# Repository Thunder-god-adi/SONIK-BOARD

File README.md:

## Pi board

Pi board is a 90% keycboard powered with Raspberry pico and rotary encoder 

- 88 keys with numpad 
- a rotary encoder switch for volume , brightness etc
- IT runs on KMK firmware

**WHY I BUILT THIS**

I built this keybaord i want to prove that i can also built something like thisa to my parents becasue they think they just waste their money by buying laptop for me.....:)

## SCHEMATICS

## PCB 

## CAD

**TOP PLATE**

**BOTTOM PLATE **

**ASSEMBLY**

**DRC**

**BOM**

| Name                | Specification   | Cost (USD) | Qty | Total (USD) | Distributor | Links
| ------------------- | --------------- | ---------- | --- | ----------- | ----------- | --------
| Stabilizers         | Stabilizers     | $11.00     | 1   | $11.00      | Neo macro     | https://neomacro.in/products/tx-stabilizers-rev-3?variant=47932019474710&country=IN&currency=INR&utm_medium=product_sync&utm_source=google&utm_content=sag_organic&utm_campaign=sag_organic&srsltid=AfmBOopAZh_3mHHek6k51stWkO01FKqth9q2Yk17Qg0eZDxcpM-QBQXmecs
| Gradient Keycaps    | Keycaps         | $15.00     | 1   | $15.00      | Stacksb     | https://stackskb.com/store/veekos-gradient-keycaps-cherry-profile-135-keys/
| Akko Botany Switch  | Keyswitcs       | $11.00     | 2   | $22.00      | Stacksb     | https://stackskb.com/store/akko-botany-switch-pack-of-45/
| Diodes              | Diodes          | $0.07      | 90  | $6.30       | Robu        | https://robu.in/product/1n4148-t50a-onsemi-100v-1v10ma-4ns-200ma-do-35-switching-diodes-rohs?gbraid=0AAAAADvLFWevvj4M4vNbmO3om0BtvR3cM&gclid=Cj0KCQjwkMjOBhC5ARIsADIdb3ejehMys0VX-rKdz88-m8GIJ9Eq1WYWfVe9zik6fVFRTgqYCsY3qzwaAh-yEALw_wcB&gad_source=4&gad_campaignid=17427802703
| Rotary encoder EC11 | Volume knob     | $1.90      | 1   | $1.90       | Amazon      | https://www.amazon.in/CentIoT-Encoder-Digital-Potentiometer-Control/dp/B0888RVZSN/ref=sr_1_2?crid=1O052ZHUZWRTI&dib=eyJ2IjoiMSJ9.cvB_S8-clwOY-fsh1jDEgX3I-TyaPGhd3iCZ3GX6_eVNqTFQ_8wSSmi1On-7sotSobE5H2o6_AdbzYdahHyzxVa2r98weRk7Xio0he5pwCPG3HprLqdHpm22K6901hNoEpE-hIGjlVB_5vPunDYkwwF-xJId0MWA8qBv0XmPnWoB6r2DHp8Y4YQ3xCR4cYbDpMEaPRt-TiNIJyYnxAqq45TIMvtyW55dE8gAhrPO1Tsw-1D0wNrqEAwxKJM0g31FXADWRofN-_3Ve-ysOmZnVKB2OWHzU1zumZQCo1mfBaE.hG0MUNhue4hmHgy-1sKEAq1MKh8FfEkSRrKNu_826tM&dib_tag=se&keywords=ec11&qid=1775385244&sprefix=%2Caps%2C418&sr=8-2
| Raspberry Pi Pico   | Microcontroller | $5.00      | 1   | $5.00       | Robocraze      | https://robocraze.com/products/raspberry-pi-pico-h-pico-with-headers-soldered?variant=43243705467104&country=IN&currency=INR&utm_medium=product_sync&utm_source=google&utm_content=sag_organic&utm_campaign=sag_organic&campaignid=17937704573&adgroupid=&keyword=&device=c&gad_source=1&gad_campaignid=17931338845&gbraid=0AAAAADgHQvZF5vM50PaT2BS6I2GJWQeId&gclid=EAIaIQobChMIytrl47SklQMVCZpmAh2yYR0KEAQYASABEgJTi_D_BwE
| PCB                 | PCB             | $33.00     | 1   | $33.00      | JLC         |
| **TOTAL**           |                 |            |     | **$95.20**  |             |
**JLC CART**

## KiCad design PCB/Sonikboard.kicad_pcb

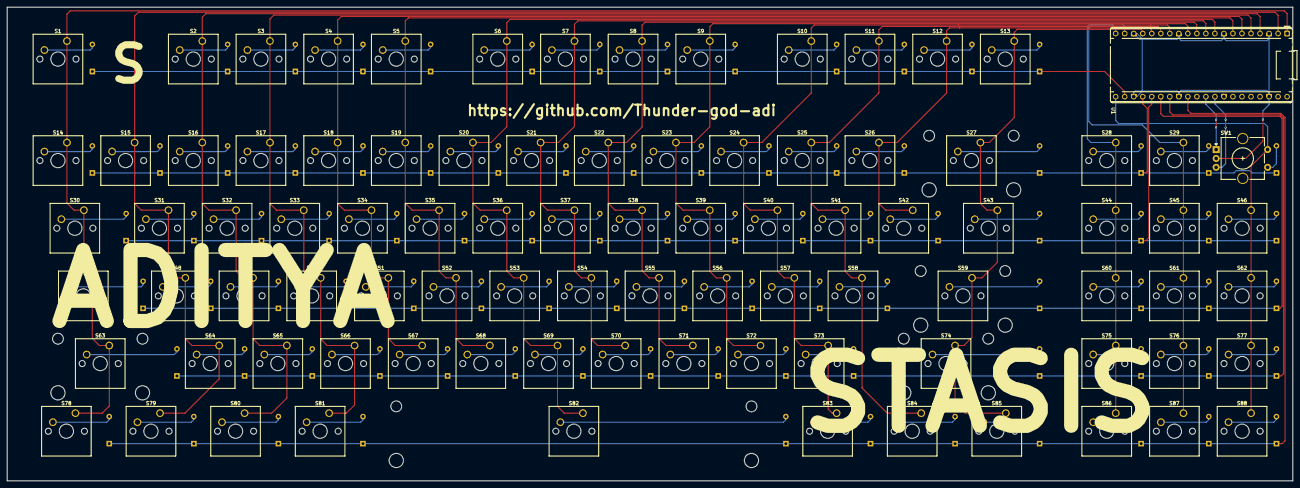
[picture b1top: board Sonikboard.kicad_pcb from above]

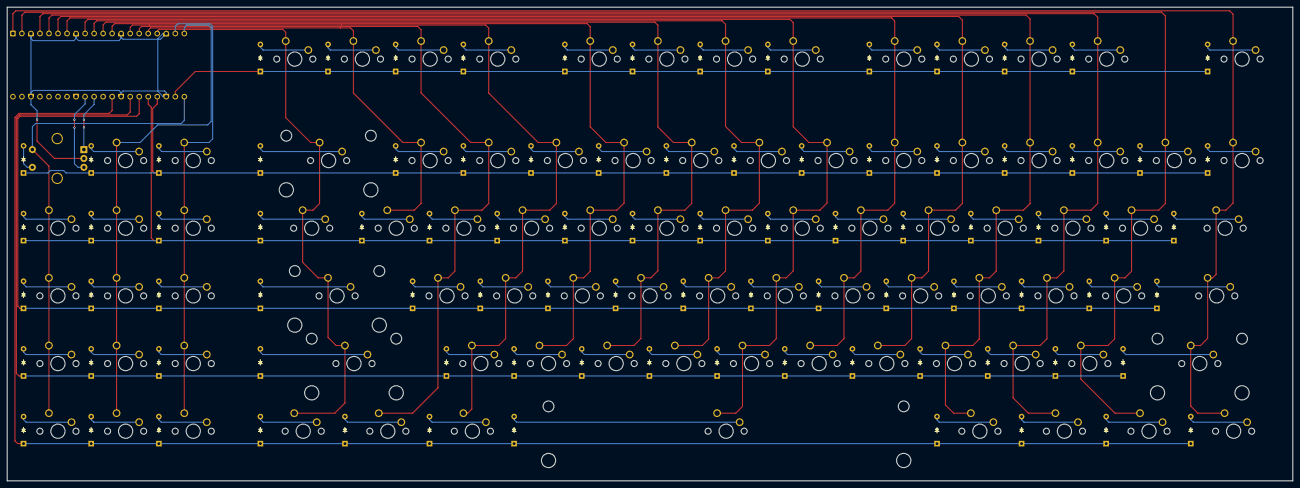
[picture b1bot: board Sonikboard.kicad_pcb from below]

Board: 2 copper layers, 361.9 x 133.4 mm, 179 parts (89 on the bottom side), 115 nets.

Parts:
D1, D2, D3, D4, D5, D6, D7, D8, D9, D10, D11, D12, D13, D14, D15, D16, D17, D18, D19, D20, D21, D22, D23, D24, D25, D26, D27, D28, D29, D30, D31, D32, D33, D34, D35, D36, D37, D38, D39, D40, D41, D42, D43, D44, D45, D46, D47, D48, D49, D50, D51, D52, D53, D54, D55, D56, D57, D58, D59, D60, D61, D62, D63, D64, D65, D66, D67, D68, D69, D70, D71, D72, D73, D74, D75, D76, D77, D78, D79, D80, D81, D82, D83, D84, D85, D86, D87, D88, D89: D_Small; Diode_DO-35
S1, S2, S3, S4, S5, S6, S7, S8, S9, S10, S11, S12, S13, S14, S15, S16, S17, S18, S19, S20, S21, S22, S23, S24, S25, S26, S28, S29, S31, S32, S33, S34, S35, S36, S37, S38, S39, S40, S41, S42, S44, S45, S46, S48, S49, S50, S51, S52, S53, S54, S55, S56, S57, S58, S60, S61, S62, S64, S65, S66, S67, S68, S69, S70, S71, S72, S73, S75, S76, S77, S86, S87, S88: Keyswitch; SW_Cherry_MX_1.00u_PCB
S27: Keyswitch; SW_Cherry_MX_2.00u_PCB
S30, S43: Keyswitch; SW_Cherry_MX_1.50u_PCB
S47: Keyswitch; SW_Cherry_MX_1.75u_PCB
S59, S63: Keyswitch; SW_Cherry_MX_2.25u_PCB
S74: Keyswitch; SW_Cherry_MX_2.75u_PCB
S78, S79, S80, S81, S83, S84, S85: Keyswitch; SW_Cherry_MX_1.25u_PCB
S82: Keyswitch; SW_Cherry_MX_6.25u_PCB
SW1: RotaryEncoder_Switch; RotaryEncoder_Alps_EC11E-Switch_Vertical_H20mm_CircularMoun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
U1: Raspberry_Pi_Pico; RaspberryPi_Pico_Common_THT

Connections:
Col 0: S1.1, S14.1, S30.1, S47.1, S63.1, S78.1, U1.1 (GPIO0)
Col 1: S15.1, S31.1, S48.1, S64.1, S79.1, U1.2 (GPIO1)
Col 2: S2.1, S16.1, S32.1, S49.1, S65.1, S80.1, U1.4 (GPIO2)
Col 3: S3.1, S17.1, S33.1, S50.1, S66.1, S81.1, U1.5 (GPIO3)
Col 4: S4.1, S18.1, S34.1, S51.1, S67.1, U1.6 (GPIO4)
Col 5: S5.1, S19.1, S35.1, S52.1, S68.1, U1.7 (GPIO5)
Col 6: S6.1, S20.1, S36.1, S53.1, S69.1, S82.1, U1.9 (GPIO6)
Col 7: S7.1, S21.1, S37.1, S54.1, S70.1, U1.10 (GPIO7)
Col 8: S8.1, S22.1, S38.1, S55.1, S71.1, U1.11 (GPIO8)
Col 9: S9.1, S23.1, S39.1, S56.1, S72.1, U1.12 (GPIO9)
Col 10: S10.1, S24.1, S40.1, S57.1, S73.1, S83.1, U1.14 (GPIO10)
Col 11: S11.1, S25.1, S41.1, S58.1, S84.1, U1.15 (GPIO11)
Col 12: S12.1, S26.1, S42.1, U1.16 (GPIO12)
Col 13: S13.1, S27.1, S43.1, S59.1, S74.1, S85.1, U1.17 (GPIO13)
Col 14: S28.1, S44.1, S60.1, S75.1, S86.1, U1.19 (GPIO14)
Col 15: S29.1, S45.1, S61.1, S76.1, S87.1, U1.20 (GPIO15)
Col 16: S46.1, S62.1, S77.1, S88.1, SW1.S2, U1.21 (GPIO16)
GND: SW1.C, U1.3 (GND), U1.8 (GND), U1.13 (GND), U1.18 (GND), U1.23 (GND), U1.28 (GND), U1.38 (GND)
unnamed: D1.2 (A), S1.2
unnamed: D2.2 (A), S2.2
unnamed: D3.2 (A), S3.2
unnamed: D4.2 (A), S4.2
unnamed: D5.2 (A), S5.2
unnamed: D6.2 (A), S6.2
unnamed: D7.2 (A), S7.2
unnamed: D8.2 (A), S8.2
unnamed: D9.2 (A), S9.2
unnamed: D10.2 (A), S10.2
unnamed: D11.2 (A), S11.2
unnamed: D12.2 (A), S12.2
unnamed: D13.2 (A), S13.2
unnamed: D14.2 (A), S14.2
unnamed: D15.2 (A), S15.2
unnamed: D16.2 (A), S16.2
unnamed: D17.2 (A), S17.2
unnamed: D18.2 (A), S18.2
unnamed: D19.2 (A), S19.2
unnamed: D20.2 (A), S20.2
unnamed: D21.2 (A), S21.2
unnamed: D22.2 (A), S22.2
unnamed: D23.2 (A), S23.2
unnamed: D24.2 (A), S24.2
unnamed: D25.2 (A), S25.2
unnamed: D26.2 (A), S26.2
unnamed: D27.2 (A), S27.2
unnamed: D28.2 (A), S28.2
unnamed: D29.2 (A), S29.2
unnamed: D30.2 (A), SW1.S1
unnamed: D31.2 (A), S30.2
unnamed: D32.2 (A), S31.2
unnamed: D33.2 (A), S32.2
unnamed: D34.2 (A), S33.2
unnamed: D35.2 (A), S34.2
unnamed: D36.2 (A), S35.2
unnamed: D37.2 (A), S36.2
unnamed: D38.2 (A), S37.2
unnamed: D39.2 (A), S38.2
unnamed: D40.2 (A), S39.2
unnamed: D41.2 (A), S40.2
unnamed: D42.2 (A), S41.2
unnamed: D43.2 (A), S42.2
unnamed: D44.2 (A), S43.2
unnamed: D45.2 (A), S44.2
unnamed: D46.2 (A), S45.2
unnamed: D47.2 (A), S46.2
unnamed: D48.2 (A), S47.2
unnamed: D49.2 (A), S48.2
unnamed: D50.2 (A), S49.2
unnamed: D51.2 (A), S50.2
unnamed: D52.2 (A), S51.2
unnamed: D53.2 (A), S52.2
unnamed: D54.2 (A), S53.2
unnamed: D55.2 (A), S54.2
unnamed: D56.2 (A), S55.2
unnamed: D57.2 (A), S56.2
unnamed: D58.2 (A), S57.2
unnamed: D59.2 (A), S58.2
unnamed: D60.2 (A), S59.2
unnamed: D61.2 (A), S60.2
unnamed: D62.2 (A), S61.2
unnamed: D63.2 (A), S62.2
unnamed: D64.2 (A), S63.2
unnamed: D65.2 (A), S64.2
unnamed: D66.2 (A), S65.2
unnamed: D67.2 (A), S66.2
unnamed: D68.2 (A), S67.2
unnamed: D69.2 (A), S68.2
unnamed: D70.2 (A), S69.2
unnamed: D71.2 (A), S70.2
unnamed: D72.2 (A), S71.2
unnamed: D73.2 (A), S72.2
unnamed: D74.2 (A), S73.2
unnamed: D75.2 (A), S74.2
unnamed: D76.2 (A), S75.2
unnamed: D77.2 (A), S76.2
unnamed: D78.2 (A), S77.2
unnamed: D79.2 (A), S78.2
unnamed: D80.2 (A), S79.2
unnamed: D81.2 (A), S80.2
unnamed: D82.2 (A), S81.2
unnamed: D83.2 (A), S82.2
unnamed: D84.2 (A), S83.2
unnamed: D85.2 (A), S84.2
unnamed: D86.2 (A), S85.2
unnamed: D87.2 (A), S86.2
unnamed: D88.2 (A), S87.2
unnamed: D89.2 (A), S88.2
RE A: SW1.A, U1.31 (GPIO26_ADC0)
RE B: SW1.B, U1.32 (GPIO27_ADC1)
Row 0: D1.1 (K), D2.1 (K), D3.1 (K), D4.1 (K), D5.1 (K), D6.1 (K), D7.1 (K), D8.1 (K), D9.1 (K), D10.1 (K), D11.1 (K), D12.1 (K), D13.1 (K), U1.22 (GPIO17)
Row 1: D14.1 (K), D15.1 (K), D16.1 (K), D17.1 (K), D18.1 (K), D19.1 (K), D20.1 (K), D21.1 (K), D22.1 (K), D23.1 (K), D24.1 (K), D25.1 (K), D26.1 (K), D27.1 (K), D28.1 (K), D29.1 (K), D30.1 (K), U1.24 (GPIO18)
Row 2: D31.1 (K), D32.1 (K), D33.1 (K), D34.1 (K), D35.1 (K), D36.1 (K), D37.1 (K), D38.1 (K), D39.1 (K), D40.1 (K), D41.1 (K), D42.1 (K), D43.1 (K), D44.1 (K), D45.1 (K), D46.1 (K), D47.1 (K), U1.25 (GPIO19)
Row 3: D48.1 (K), D49.1 (K), D50.1 (K), D51.1 (K), D52.1 (K), D53.1 (K), D54.1 (K), D55.1 (K), D56.1 (K), D57.1 (K), D58.1 (K), D59.1 (K), D60.1 (K), D61.1 (K), D62.1 (K), D63.1 (K), U1.26 (GPIO20)
Row 4: D64.1 (K), D65.1 (K), D66.1 (K), D67.1 (K), D68.1 (K), D69.1 (K), D70.1 (K), D71.1 (K), D72.1 (K), D73.1 (K), D74.1 (K), D75.1 (K), D76.1 (K), D77.1 (K), D78.1 (K), U1.27 (GPIO21)
Row 5: D79.1 (K), D80.1 (K), D81.1 (K), D82.1 (K), D83.1 (K), D84.1 (K), D85.1 (K), D86.1 (K), D87.1 (K), D88.1 (K), D89.1 (K), U1.29 (GPIO22)
